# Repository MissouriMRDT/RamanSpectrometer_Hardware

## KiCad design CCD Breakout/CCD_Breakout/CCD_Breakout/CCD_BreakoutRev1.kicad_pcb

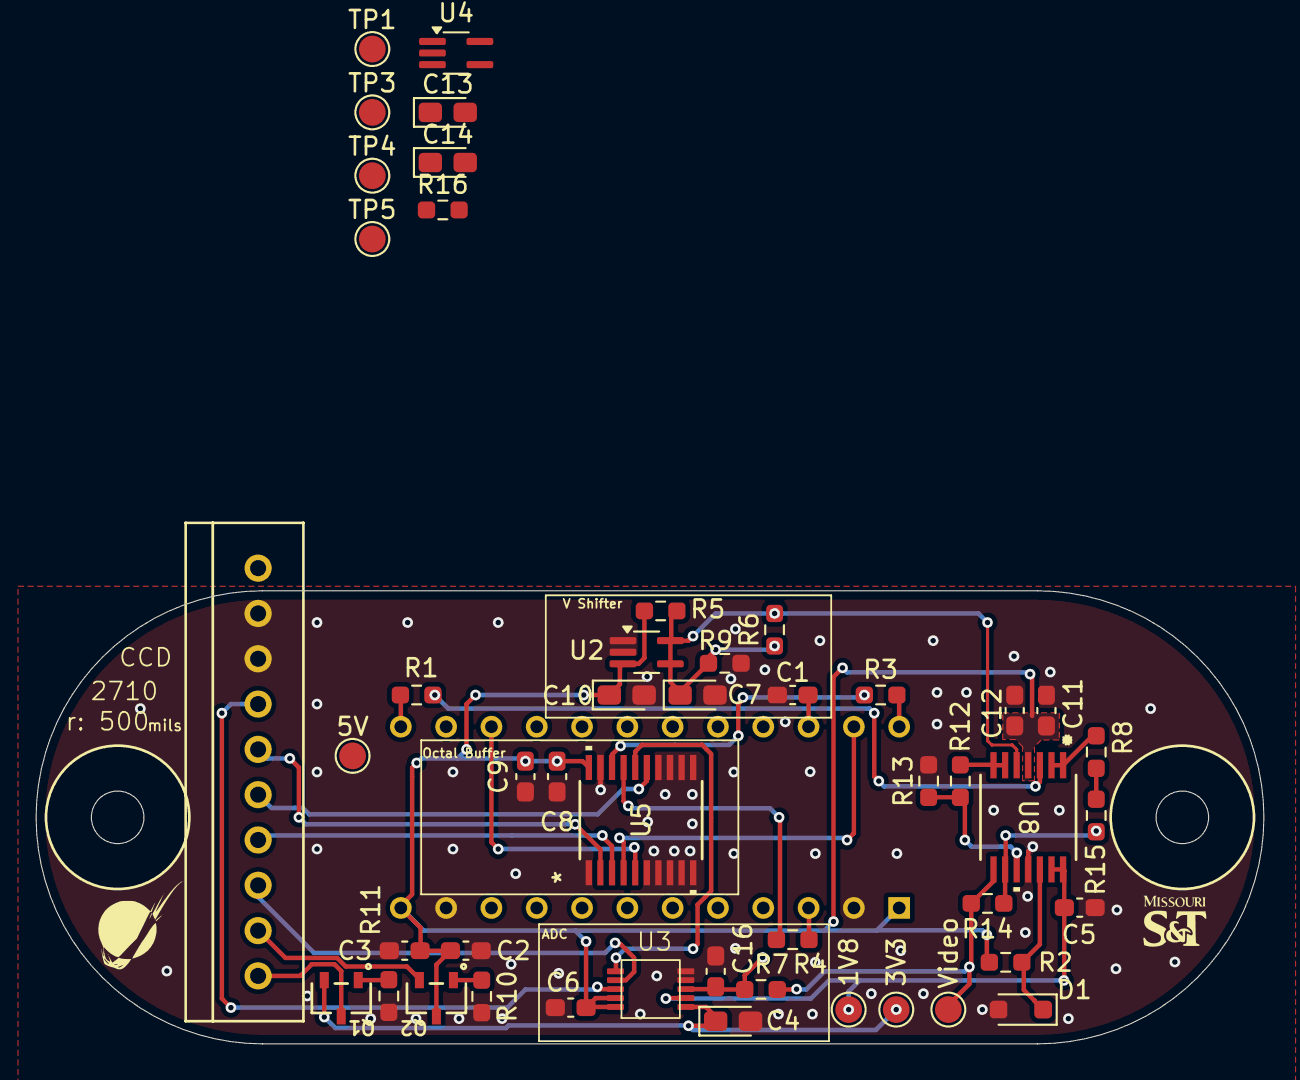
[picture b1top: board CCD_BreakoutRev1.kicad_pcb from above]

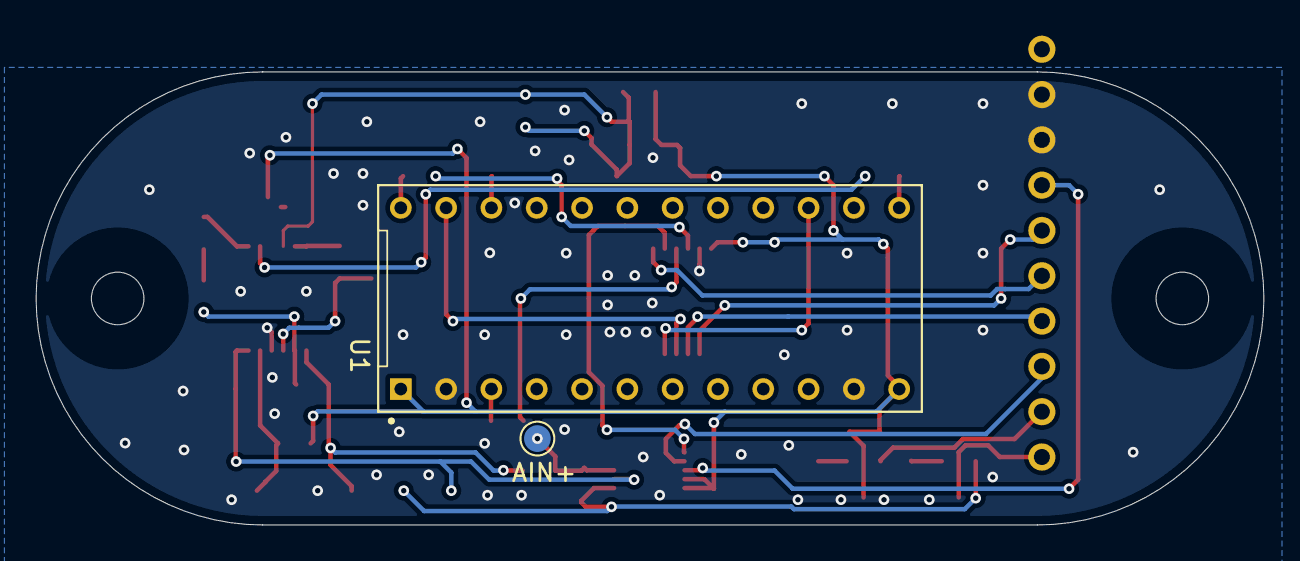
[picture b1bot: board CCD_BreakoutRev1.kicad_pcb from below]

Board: 2 copper layers, 68.8 x 25.4 mm, 52 parts (2 on the bottom side), 34 nets.

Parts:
1V8: 1V8; TestPoint_Pad_D1.5mm
3V3: 3V3; TestPoint_Pad_D1.5mm
5V: 5V; TestPoint_Pad_D1.5mm
AIN+: AIN+; TestPoint_Pad_D1.5mm
C1, C5: 1uF; C_0603_1608Metric_Pad1.08x0.95mm_HandSolder
C2, C8, C11: .01uF; C_0603_1608Metric_Pad1.08x0.95mm_HandSolder
C3, C9, C12: 22uF; C_0603_1608Metric_Pad1.08x0.95mm_HandSolder
C4: 10uF; CP_EIA-2012-12_Kemet-R_HandSolder
C6: .1uF; C_0603_1608Metric_Pad1.08x0.95mm_HandSolder
C7, C14: 0.47uF; CP_EIA-2012-12_Kemet-R_HandSolder
C10, C13: 0.1uF; CP_EIA-2012-12_Kemet-R_HandSolder
C16: 2.2nF; C_0603_1608Metric_Pad1.08x0.95mm_HandSolder
Conn1: Molex_SL_10; MOLEX_SL_10_Vertical
D1: CMDZ1L8; D_SOD-323_HandSoldering
H1, H2: 4_40_Hole
Q1, Q2: SI01P10-TP; SOT-23_MCC-L
R1: 100; R_0603_1608Metric_Pad0.98x0.95mm_HandSolder
R2, R5, R10, R11, R14: 1k; R_0603_1608Metric_Pad0.98x0.95mm_HandSolder
R3, R4: 82; R_0603_1608Metric_Pad0.98x0.95mm_HandSolder
R6, R15: 10k; R_0603_1608Metric_Pad0.98x0.95mm_HandSolder
R7: 15; R_0603_1608Metric_Pad0.98x0.95mm_HandSolder
R8: 51; R_0603_1608Metric_Pad0.98x0.95mm_HandSolder
R9: 15k; R_0603_1608Metric_Pad0.98x0.95mm_HandSolder
R12: 22k; R_0603_1608Metric_Pad0.98x0.95mm_HandSolder
R13: 33k; R_0603_1608Metric_Pad0.98x0.95mm_HandSolder
R16: 20k; R_0603_1608Metric_Pad0.98x0.95mm_HandSolder
TP1: 1V8; TestPoint_Pad_D1.5mm
TP3: 3V3; TestPoint_Pad_D1.5mm
TP4: AIN+; TestPoint_Pad_D1.5mm
TP5: Video; TestPoint_Pad_D1.5mm
U1: CCD; ED90055-ND
U2, U4: SOT-353_SC-70-5_Handsoldering
U3: ADC-MCP33151; Untitled
U5: 74HC541PW_118
U8: OPA4322AIPWR
Video: Video; TestPoint_Pad_D1.5mm

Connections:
+1V8: 1V8.1, C5.1, TP1.1, U3.2 (AVDD), U8.13 (IND-), U8.14 (OUTD)
+3V3: 3V3.1, C6.1, Q1.2 (S), U3.10 (DVIO)
+5V: 5V.1, C2.1, C3.1, C4.1, C8.1, C9.1, C10.1, C11.1, C12.1, C13.1, Q2.3 (D), R2.1, R5.1, R14.1, TP3.1, U1.1 (Vdd), U1.12 (Vdd), U2.3 (IN), U3.1 (VREF), U4.3 (IN), U5.20 (VCC), U8.4 (V+)
/ADC/CLK2: Conn1.7, U3.8 (SCLK)
/ADC/OUT: Conn1.3, U3.7 (SDO)
/ADC/SDI: Conn1.8, U3.9 (SDI)
/ADC/TRIG: Conn1.9, U3.6 (CNVST)
/ADC/Video: R7.1, R13.2, TP5.1, U8.8 (OUTC), Video.1
/ADC/opIND+: C14.1, D1.1 (K), R2.2, R14.2, R15.2, U4.5, U8.12 (IND+)
/CCD/CLK: Conn1.4, U5.3 (A1)
/CCD/CLKb: R4.2, U5.17 (Y1)
/CCD/EOSb: U1.15 (EOS), U5.5 (A3)
/CCD/ST: Conn1.6, U5.2 (A0)
/CCD/STb: R3.1, U5.18 (Y0)
/CCD/Trig: Conn1.5, U5.16 (Y2)
/CCD/Trigb: U1.23 (Trig), U5.4 (A2)
/CCD/Videob: R8.1, U8.10 (INC+)
/CCD/opINA+: R1.1, U8.3 (INA+)
/CCD/opINA-: R8.2, U8.1 (OUTA), U8.2 (INA-)
/CCD/opINB+: C7.1, R5.2, R6.2, U2.5, U8.5 (INB+)
/CCD/opINB-: R12.1, U8.6 (INB-), U8.7 (OUTB)
/CCD/opINC-: R12.2, R13.1, U8.9 (INC-)
GND: C1.2, C2.2, C3.2, C4.2, C5.2, C6.2, C7.2, C8.2, C9.2, C10.2, C11.2, C12.2, C13.2, C14.2, C16.2, Conn1.10, D1.2 (A), R9.1, R10.2, R11.2, R16.1, U1.2 (Vss), U1.11 (Vss), U2.1, U2.2, U3.4 (AIN-), U3.5 (GND), U4.1, U4.2, U5.1 (OE1), U5.6 (A4), U5.7 (A5), U5.8 (A6), U5.9 (A7), U5.10 (GND), U5.11 (Y7), U5.12 (Y6), U5.13 (Y5), U5.14 (Y4), U5.19 (OE2), U8.11 (V-)
unnamed: Conn1.1, Q1.3 (D)
unnamed: Q1.1 (G), R11.1
unnamed: Q2.1 (G), R10.1
unnamed: Conn1.2, Q2.2 (S)
unnamed: R6.1, R9.2, U2.4
unnamed: R15.1, R16.2, U4.4
unnamed: R4.1, U1.3 (CLK)
unnamed: R3.2, U1.24 (ST)
unnamed: C1.1, U1.22 (VIcp)
unnamed: R1.2, U1.13 (Video)
unnamed: AIN+.1, C16.1, R7.2, TP4.1, U3.3 (AIN+)

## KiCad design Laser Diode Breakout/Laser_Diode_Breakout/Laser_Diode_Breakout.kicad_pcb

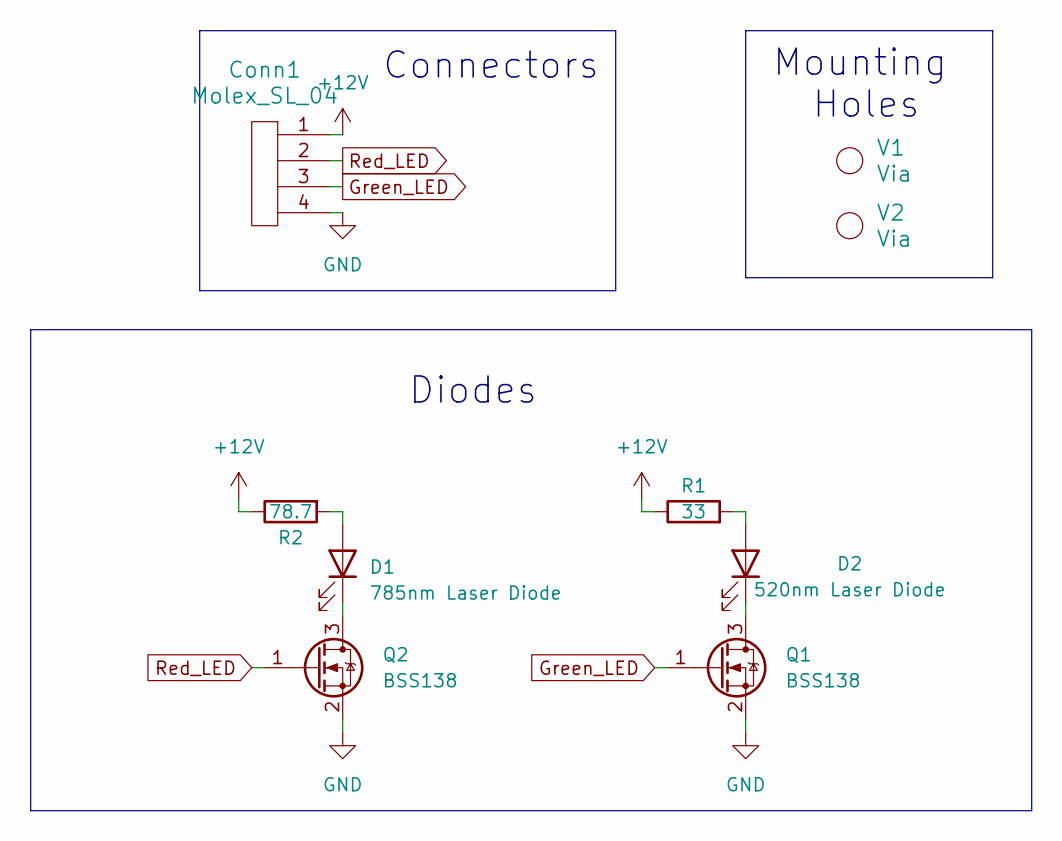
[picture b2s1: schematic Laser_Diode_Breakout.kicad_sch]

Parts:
Conn1: Molex_SL_04; MOLEX_SL_04_Vertical
D1: 785nm Laser Diode
D2: 520nm Laser Diode; PLT5520B - 520nm
Q1, Q2: BSS138; SOT-23
R1: 33; R_2512_6332Metric_Pad1.40x3.35mm_HandSolder
R2: 78.7; R_1206_3216Metric_Pad1.30x1.75mm_HandSolder
V1, V2: Via; 4_40_Hole

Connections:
+12V: Conn1.1, R1.1, R2.1
GND: Conn1.4, Q1.2 (S), Q2.2 (S)
Green_LED: Conn1.3, Q1.1 (G)
unnamed: D1.2 (A), R2.2
unnamed: D1.1 (K), Q2.3 (D)
unnamed: D2.2 (A), R1.2
unnamed: D2.1 (K), Q1.3 (D)
Red_LED: Conn1.2, Q2.1 (G)

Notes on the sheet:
Mounting Holes
Connectors
Diodes

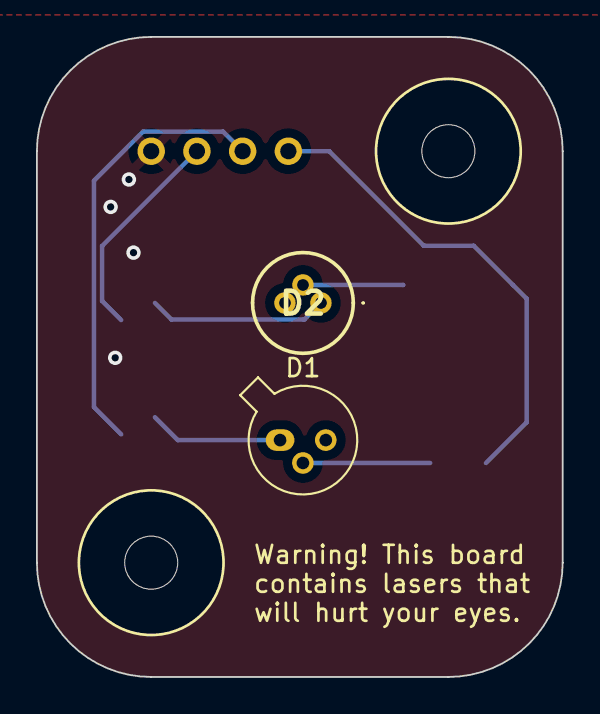
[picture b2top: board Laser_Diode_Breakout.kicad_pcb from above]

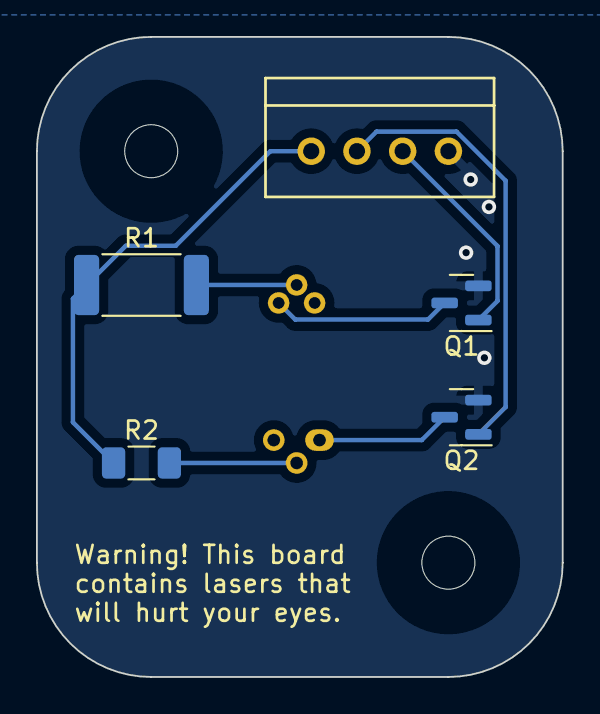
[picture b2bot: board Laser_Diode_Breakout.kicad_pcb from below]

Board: 2 copper layers, 29.2 x 35.6 mm, 9 parts (5 on the bottom side), 8 nets.

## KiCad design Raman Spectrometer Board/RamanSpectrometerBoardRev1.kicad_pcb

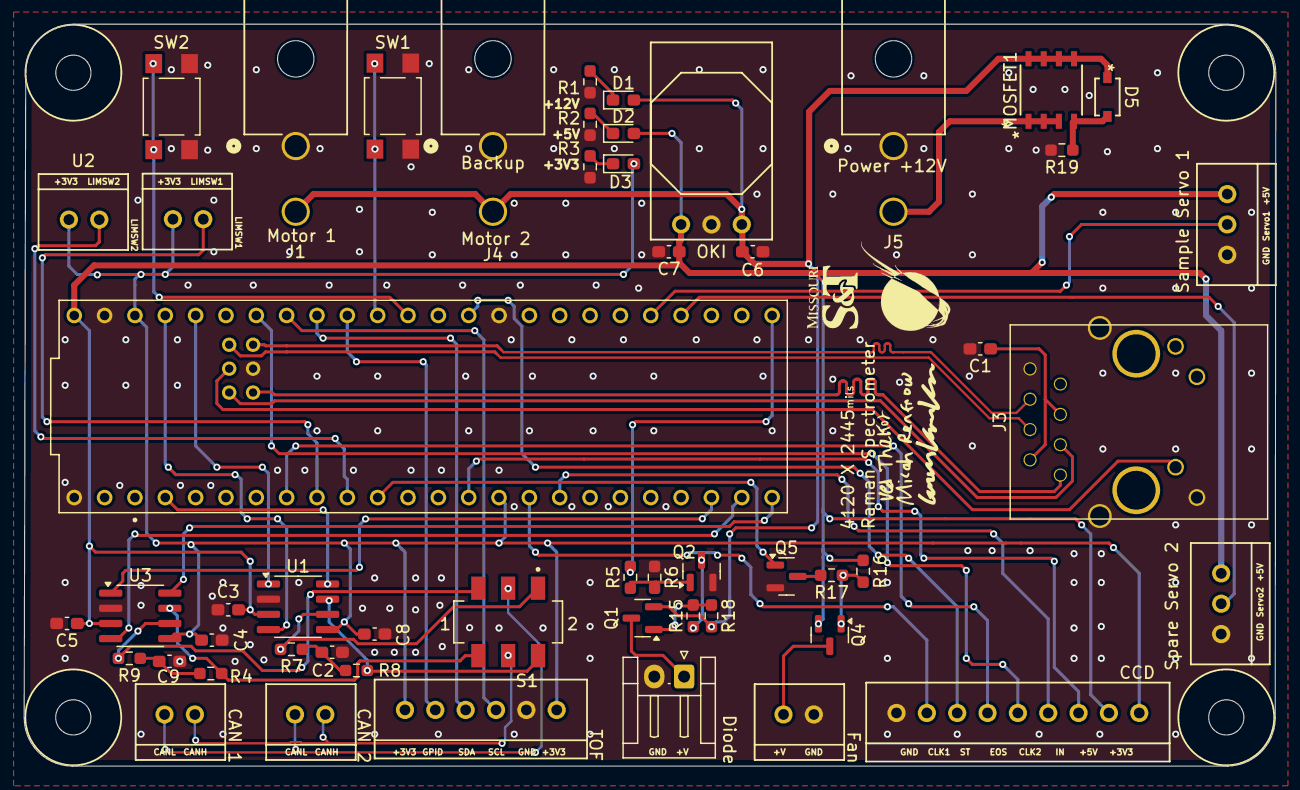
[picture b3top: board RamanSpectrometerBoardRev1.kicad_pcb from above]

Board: 2 copper layers, 104.8 x 62.1 mm, 57 parts (0 on the bottom side), 53 nets.

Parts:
C1: .1uF; C_0603_1608Metric_Pad1.08x0.95mm_HandSolder
C2, C9: 4.7nf; C_0603_1608Metric_Pad1.08x0.95mm_HandSolder
C3, C4, C5, C8: 100n; C_0603_1608Metric_Pad1.08x0.95mm_HandSolder
C6, C7: 10uF; C_0603_1608Metric_Pad1.08x0.95mm_HandSolder
Conn1, Conn2, Conn4, Conn6, Conn7: Molex_SL_02; MOLEX_SL_02_Vertical
Conn3: Molex_SL_09; MOLEX_SL_09_Vertical
Conn5: Molex_SL_06; MOLEX_SL_06_Vertical
D1, D2, D3: Green LED; LED_0603_1608Metric_Pad1.05x0.95mm_HandSolder
D5: MMSZ5240BT1G; SOD-123_ONS-L
H1, H2, H3, H4: MountingHole; 4_40_Hole_Corner
J1, J4, J5: 768250002; CONN_SD-76825-0100_02_MOL
J2: Conn_01x02; JST_EH_S2B-EH_1x02_P2.50mm_Horizontal
J3: RJ45_LED_Shielded; RJ45_Teensy
MOSFET1: TPC8132_LQS; SOP-8_TOS-L
Q1, Q4: AO3401A; SOT-23
Q2, Q5: BSS138; SOT-23
R1: 2.2K; R_0603_1608Metric_Pad0.98x0.95mm_HandSolder
R2: 820; R_0603_1608Metric_Pad0.98x0.95mm_HandSolder
R3: 330; R_0603_1608Metric_Pad0.98x0.95mm_HandSolder
R4, R7, R8, R9: 60; R_0603_1608Metric_Pad0.98x0.95mm_HandSolder
R5, R15: 100; R_0603_1608Metric_Pad0.98x0.95mm_HandSolder
R6, R18: 100k; R_0603_1608Metric_Pad0.98x0.95mm_HandSolder
R16, R17: 10k; R_0603_1608Metric_Pad0.98x0.95mm_HandSolder
R19: 1k; R_0603_1608Metric_Pad0.98x0.95mm_HandSolder
S1: SLW-913535-2A-SMT; SW_SLW-913535-2A-SMT
SW1, SW2: SW_Push; SW_SPST_TL3305A
ServoCon2: Molex_SL_03; MOLEX_SL_03_Vertical
ServoConn1: Molex_SL_03; MOLEX_SL_03_Vertical
U1, U3: ATA6561; SOIC-8_3.9x4.9mm_P1.27mm
U2: Teensy4.1_DEV-16771; Teensy_4_1_Ethernet
U4: OKI; OKI_Horizontal

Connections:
+3V3: C4.1, C8.1, Conn3.1, Conn4.1, Conn5.1, Conn5.6, Conn6.1, D3.2 (A), U1.5 (VIO), U2.3.3V_1 (3.3V), U2.3.3V_2 (3.3V), U3.5 (VIO)
+5V: C3.1, C5.1, C7.1, Conn3.2, D2.2 (A), Q4.2 (S), R16.1, ServoCon2.1, ServoConn1.1, U1.3 (VCC), U2.VIN, U3.3 (VCC), U4.3 (Vo)
+12V: C6.1, D1.2 (A), D5.1, J1.2, J4.2, MOSFET1.5 (DRAIN), MOSFET1.6 (DRAIN), MOSFET1.7 (DRAIN), MOSFET1.8 (DRAIN), Q1.2 (S), R18.2, U4.1 (Vi)
/CAN Transceiver/RXD: U1.4 (RXD), U2.23 (A9)
/CAN Transceiver/RXD2: U2.31 (CTX3), U3.4 (RXD)
/CAN Transceiver/STBY: U1.8 (STBY), U2.2 (OUT2)
/CAN Transceiver/STBY2: U2.32 (OUT1B), U3.8 (STBY)
/CAN Transceiver/SW1: SW2.1, U2.15 (A1)
/CAN Transceiver/SW2_Spare: SW1.1, U2.16 (A2)
/CAN Transceiver/TXD: U1.1 (TXD), U2.22 (A8)
/CAN Transceiver/TXD2: U2.30 (CRX3), U3.1 (TXD)
/CCD Breakout/ADC_CLK_3V3: Conn3.7, U2.13 (SCK)
/CCD Breakout/CCD_CLK_3V3: Conn3.4, U2.25 (A11)
/CCD Breakout/IN: Conn3.3, U2.12 (MISO)
/CCD Breakout/SDI: Conn3.8, U2.24 (A10)
/CCD Breakout/ST: Conn3.6, U2.6 (OUT1D)
/CCD Breakout/Trig: Conn3.5, U2.20 (A6)
/Connectors/D1: Conn4.2, U2.7 (RX2)
/Connectors/D2: Conn6.2, U2.8 (TX2)
/Connectors/GPID: Conn5.5, U2.17 (A3)
/Connectors/SCL: Conn5.3, U2.19 (A5)
/Connectors/SDA: Conn5.4, U2.18 (A4)
/Connectors/diodeOutput(3.3v): R5.2, U2.33 (MCLK2)
/Connectors/fanOut: Q5.1 (G), U2.9 (OUT1C)
/MCU/LED: J3.10, U2.LED
/MCU/R+: J3.4, U2.R+
/MCU/R-: J3.6, U2.R-
/MCU/Servo1: ServoConn1.2, U2.37 (CS3)
/MCU/Servo2: ServoCon2.2, U2.36 (CS2)
/MCU/T+: J3.1, U2.T+
/MCU/T-: J3.3, U2.T-
GND: C1.2, C2.2, C3.2, C4.2, C5.2, C6.2, C7.2, C8.2, C9.2, Conn3.9, Conn5.2, Conn7.1, J1.1, J2.2, J3.8, J3.9, J3.SH, J4.1, J5.1, Q2.2 (S), Q5.2 (S), R1.2, R2.2, R3.2, R6.1, R19.2, SW1.2, SW2.2, ServoCon2.3, ServoConn1.3, U1.2 (GND), U2.GND1 (GND), U2.GND2 (GND), U2.GND3 (GND), U2.GND5 (GND), U3.2 (GND), U4.2 (GND)
unnamed: C1.1, J3.2, J3.5
unnamed: C2.1, R7.1, R8.2
unnamed: C9.1, R4.2, R9.1
unnamed: Conn1.1, Conn2.1, S1.5
unnamed: Conn1.2, Conn2.2, S1.2
unnamed: D1.1 (K), R1.1
unnamed: D2.1 (K), R2.1
unnamed: D3.1 (K), R3.1
unnamed: J2.1, Q1.3 (D)
unnamed: J5.2, MOSFET1.1 (SOURCE), MOSFET1.2 (SOURCE), MOSFET1.3 (SOURCE)
unnamed: D5.2, MOSFET1.4 (GATE), R19.1
unnamed: Q1.1 (G), R15.2, R18.1
unnamed: Q2.3 (D), R15.1
unnamed: Q2.1 (G), R5.1, R6.2
unnamed: Conn7.2, Q4.3 (D)
unnamed: Q4.1 (G), R16.2, R17.1
unnamed: Q5.3 (D), R17.2
unnamed: R8.1, S1.4, U1.7 (CANH)
unnamed: R7.2, S1.1, U1.6 (CANL)
unnamed: R4.1, S1.6, U3.7 (CANH)
unnamed: R9.2, S1.3, U3.6 (CANL)
